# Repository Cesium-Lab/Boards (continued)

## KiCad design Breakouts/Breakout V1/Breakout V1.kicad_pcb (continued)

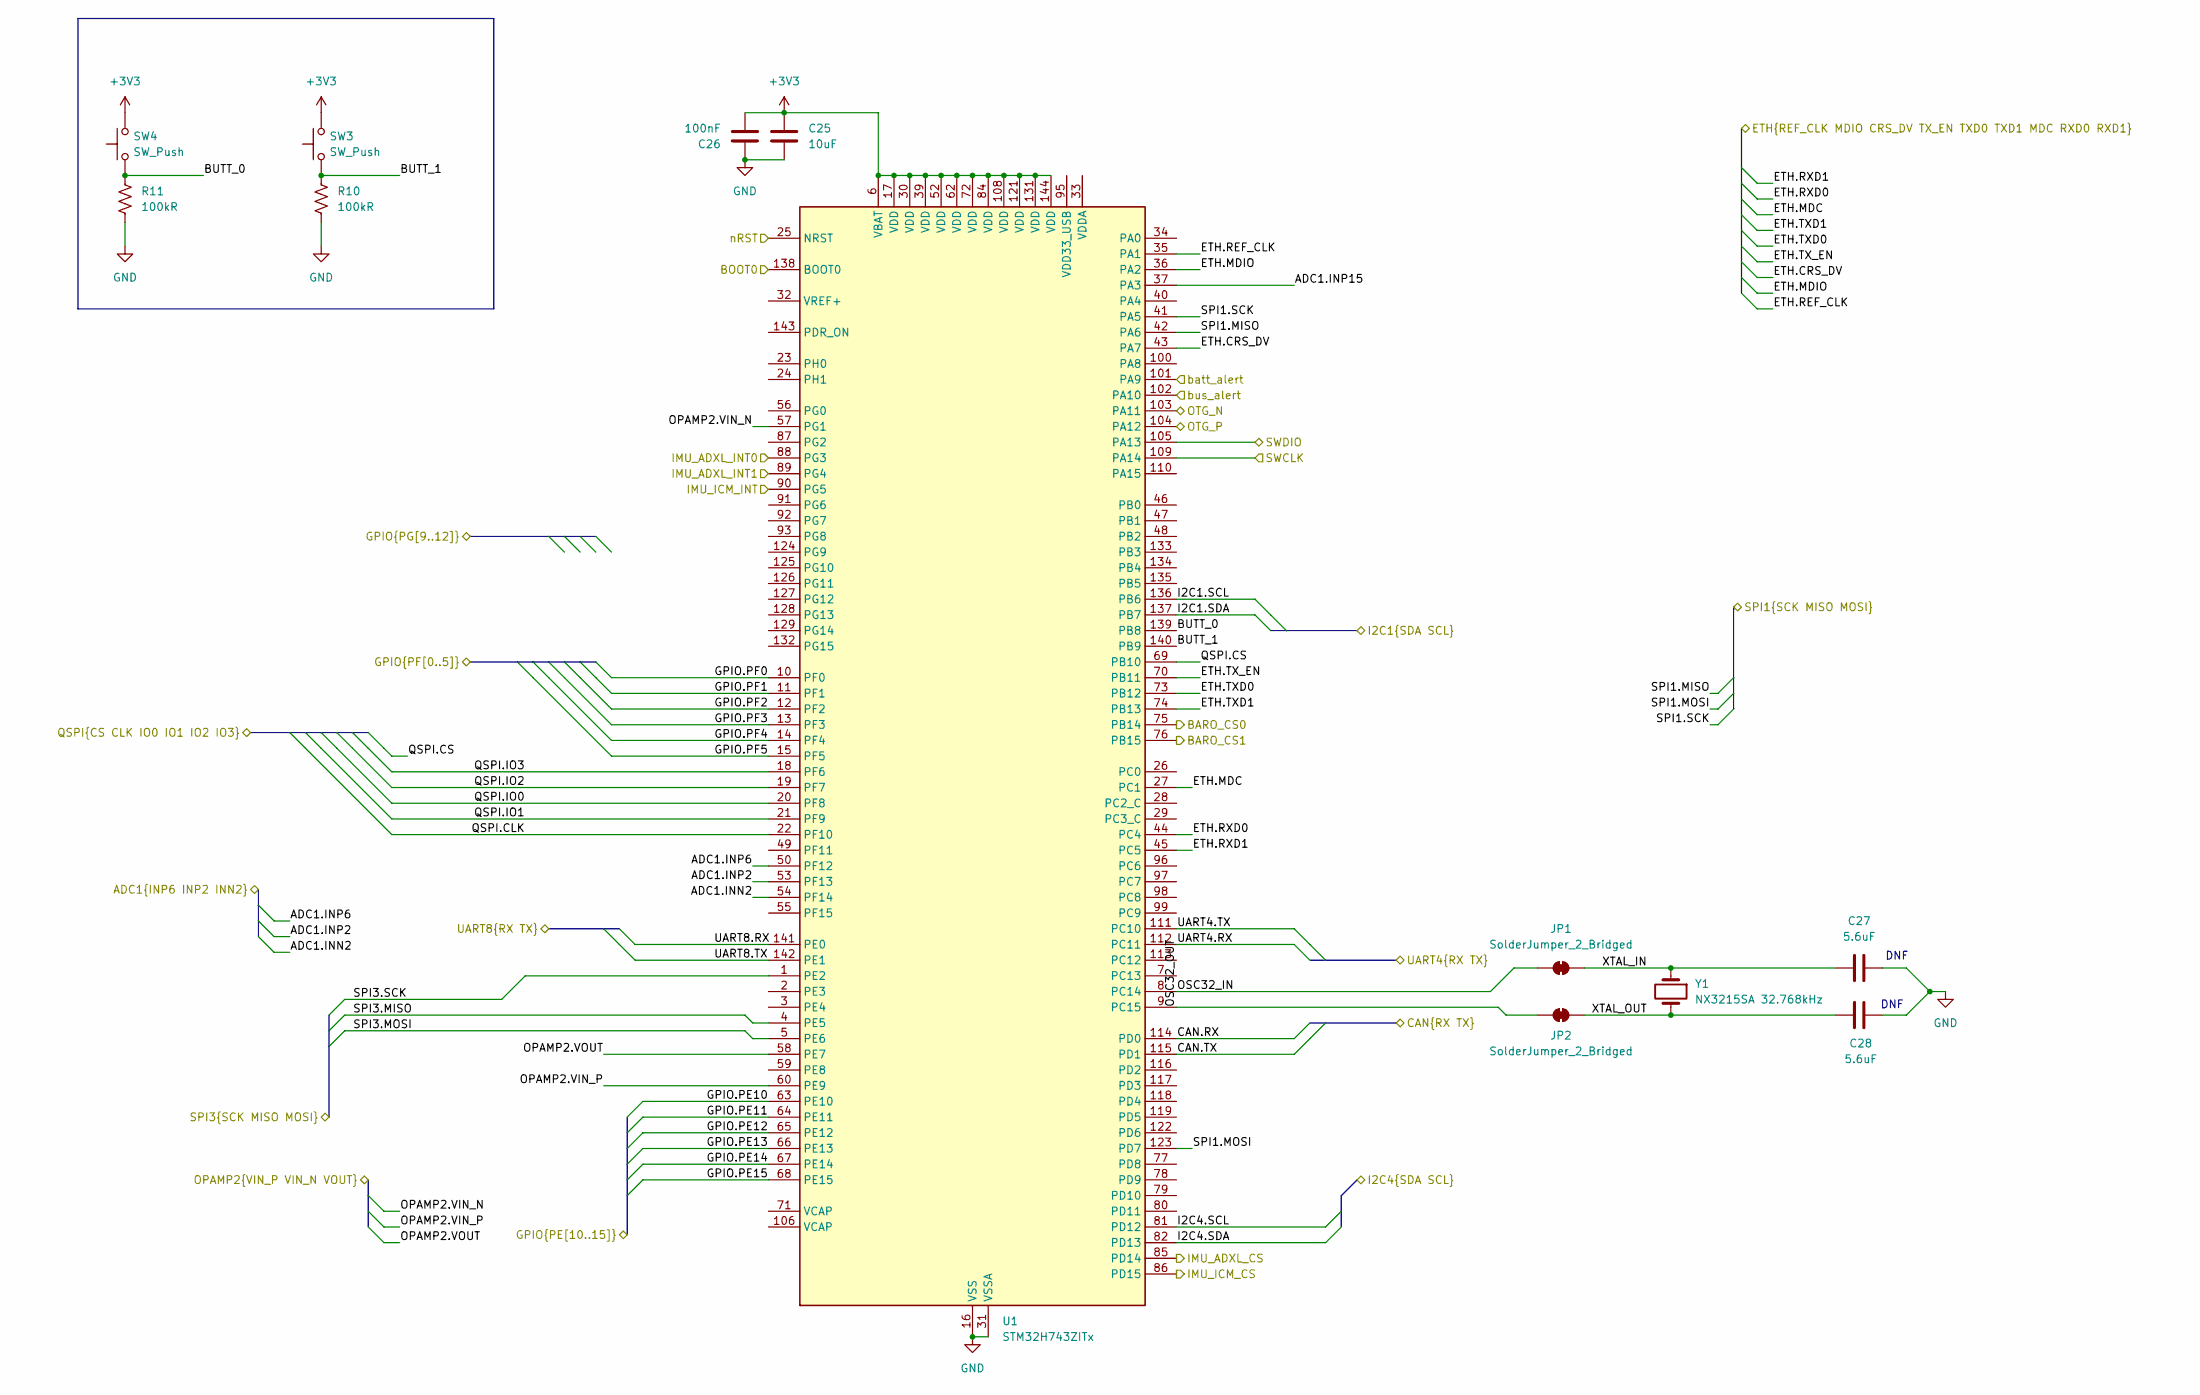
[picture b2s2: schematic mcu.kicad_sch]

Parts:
C25: 10uF; C_0603_1608Metric
C26: 100nF; C_0603_1608Metric
C27, C28: 5.6uF; C_0603_1608Metric
JP1, JP2: SolderJumper_2_Bridged; SolderJumper-2_P1.3mm_Bridged_Pad1.0x1.5mm
R10, R11: 100kR; R_0603_1608Metric
SW3, SW4: SW_Push; SW_SPST_EVPBF
U1: STM32H743ZITx; LQFP-144_20x20mm_P0.5mm
Y1: NX3215SA 32.768kHz; L_1206_3216Metric

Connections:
+3V3: C25.1, C26.2, SW3.2, SW4.2, U1.6 (VBAT), U1.17 (VDD), U1.30 (VDD), U1.39 (VDD), U1.52 (VDD), U1.62 (VDD), U1.72 (VDD), U1.84 (VDD), U1.108 (VDD), U1.121 (VDD), U1.131 (VDD), U1.144 (VDD); also elsewhere on the board
/ADXL375/CS: U1.85 (PD14); also elsewhere on the board
/ADXL375/INT1: U1.89 (PG4); also elsewhere on the board
/ADXL375/INT2: U1.88 (PG3); also elsewhere on the board
/ADXL375/SPI.MISO: U1.4 (PE5); also elsewhere on the board
/ADXL375/SPI.MOSI: U1.5 (PE6); also elsewhere on the board
/ADXL375/SPI.SCK: U1.1 (PE2); also elsewhere on the board
/Ethernet/ETH.CRS_DV: U1.43 (PA7); also elsewhere on the board
/Ethernet/ETH.MDC: U1.27 (PC1); also elsewhere on the board
/Ethernet/ETH.MDIO: U1.36 (PA2); also elsewhere on the board
/Ethernet/ETH.REF_CLK: U1.35 (PA1); also elsewhere on the board
/Ethernet/ETH.RXD0: U1.44 (PC4); also elsewhere on the board
/Ethernet/ETH.RXD1: U1.45 (PC5); also elsewhere on the board
/Ethernet/ETH.TXD0: U1.73 (PB12); also elsewhere on the board
/Ethernet/ETH.TXD1: U1.74 (PB13); also elsewhere on the board
/Ethernet/ETH.TX_EN: U1.70 (PB11); also elsewhere on the board
/Extras/ADC1.INN2: U1.54 (PF14); also elsewhere on the board
/Extras/ADC1.INP2: U1.53 (PF13); also elsewhere on the board
/Extras/ADC1.INP6: U1.50 (PF12); also elsewhere on the board
/Extras/GPIO.PE10: U1.63 (PE10); also elsewhere on the board
/Extras/GPIO.PE11: U1.64 (PE11); also elsewhere on the board
/Extras/GPIO.PE12: U1.65 (PE12); also elsewhere on the board
/Extras/GPIO.PE13: U1.66 (PE13); also elsewhere on the board
/Extras/GPIO.PE14: U1.67 (PE14); also elsewhere on the board
/Extras/GPIO.PE15: U1.68 (PE15); also elsewhere on the board
/Extras/GPIO.PF0: U1.10 (PF0); also elsewhere on the board
/Extras/GPIO.PF1: U1.11 (PF1); also elsewhere on the board
/Extras/GPIO.PF2: U1.12 (PF2); also elsewhere on the board
/Extras/GPIO.PF3: U1.13 (PF3); also elsewhere on the board
/Extras/GPIO.PF4: U1.14 (PF4); also elsewhere on the board
/Extras/GPIO.PF5: U1.15 (PF5); also elsewhere on the board
/Extras/OPAMP2.VIN_N: U1.57 (PG1); also elsewhere on the board
/Extras/OPAMP2.VIN_P: U1.60 (PE9); also elsewhere on the board
/Extras/OPAMP2.VOUT: U1.58 (PE7); also elsewhere on the board
/Extras/QSPI.CLK: U1.22 (PF10); also elsewhere on the board
/Extras/QSPI.CS: U1.69 (PB10); also elsewhere on the board
/Extras/QSPI.IO0: U1.20 (PF8); also elsewhere on the board
/Extras/QSPI.IO1: U1.21 (PF9); also elsewhere on the board
/Extras/QSPI.IO2: U1.19 (PF7); also elsewhere on the board
/Extras/QSPI.IO3: U1.18 (PF6); also elsewhere on the board
/Flashing/BOOT0: U1.138 (BOOT0); also elsewhere on the board
/Flashing/D+: U1.104 (PA12); also elsewhere on the board
/Flashing/D-: U1.103 (PA11); also elsewhere on the board
/Flashing/SWCLK: U1.109 (PA14); also elsewhere on the board
/Flashing/SWDIO: U1.105 (PA13); also elsewhere on the board
/Flashing/nRST: U1.25 (NRST); also elsewhere on the board
/IMU (2g-16g)/CS: U1.86 (PD15); also elsewhere on the board
/IMU (2g-16g)/INT: U1.90 (PG5); also elsewhere on the board
/MCU/ADC1.INP15: U1.37 (PA3)
/MCU/BARO_CS0: U1.75 (PB14); also elsewhere on the board
/MCU/BARO_CS1: U1.76 (PB15); also elsewhere on the board
/MCU/BUTT_0: R11.1, SW4.1, U1.139 (PB8)
/MCU/BUTT_1: R10.1, SW3.1, U1.140 (PB9)
/MCU/CAN.RX: U1.114 (PD0); also elsewhere on the board
/MCU/CAN.TX: U1.115 (PD1); also elsewhere on the board
/MCU/I2C1.SCL: U1.136 (PB6); also elsewhere on the board
/MCU/I2C1.SDA: U1.137 (PB7); also elsewhere on the board
/MCU/I2C4.SCL: U1.81 (PD12); also elsewhere on the board
/MCU/I2C4.SDA: U1.82 (PD13); also elsewhere on the board
/MCU/OSC32_IN: JP1.1 (A), U1.8 (PC14)
/MCU/OSC32_OUT: JP2.1 (A), U1.9 (PC15)
/MCU/SPI1.MISO: U1.42 (PA6); also elsewhere on the board
/MCU/SPI1.MOSI: U1.123 (PD7); also elsewhere on the board
/MCU/SPI1.SCK: U1.41 (PA5); also elsewhere on the board
/MCU/UART4.RX: U1.112 (PC11); also elsewhere on the board
/MCU/UART4.TX: U1.111 (PC10); also elsewhere on the board
/MCU/UART8.RX: U1.141 (PE0); also elsewhere on the board
/MCU/UART8.TX: U1.142 (PE1); also elsewhere on the board
/MCU/XTAL_IN: C27.1, JP1.2 (B), Y1.1
/MCU/XTAL_OUT: C28.1, JP2.2 (B), Y1.2
/MCU/batt_alert: U1.101 (PA9); also elsewhere on the board
/MCU/bus_alert: U1.102 (PA10); also elsewhere on the board
GND: C25.2, C26.1, C27.2, C28.2, R10.2, R11.2, U1.16 (VSS), U1.31 (VSSA), U1.38 (VSS), U1.51 (VSS), U1.61 (VSS), U1.83 (VSS), U1.94 (VSS), U1.107 (VSS), U1.120 (VSS), U1.130 (VSS); also elsewhere on the board

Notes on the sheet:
DNF

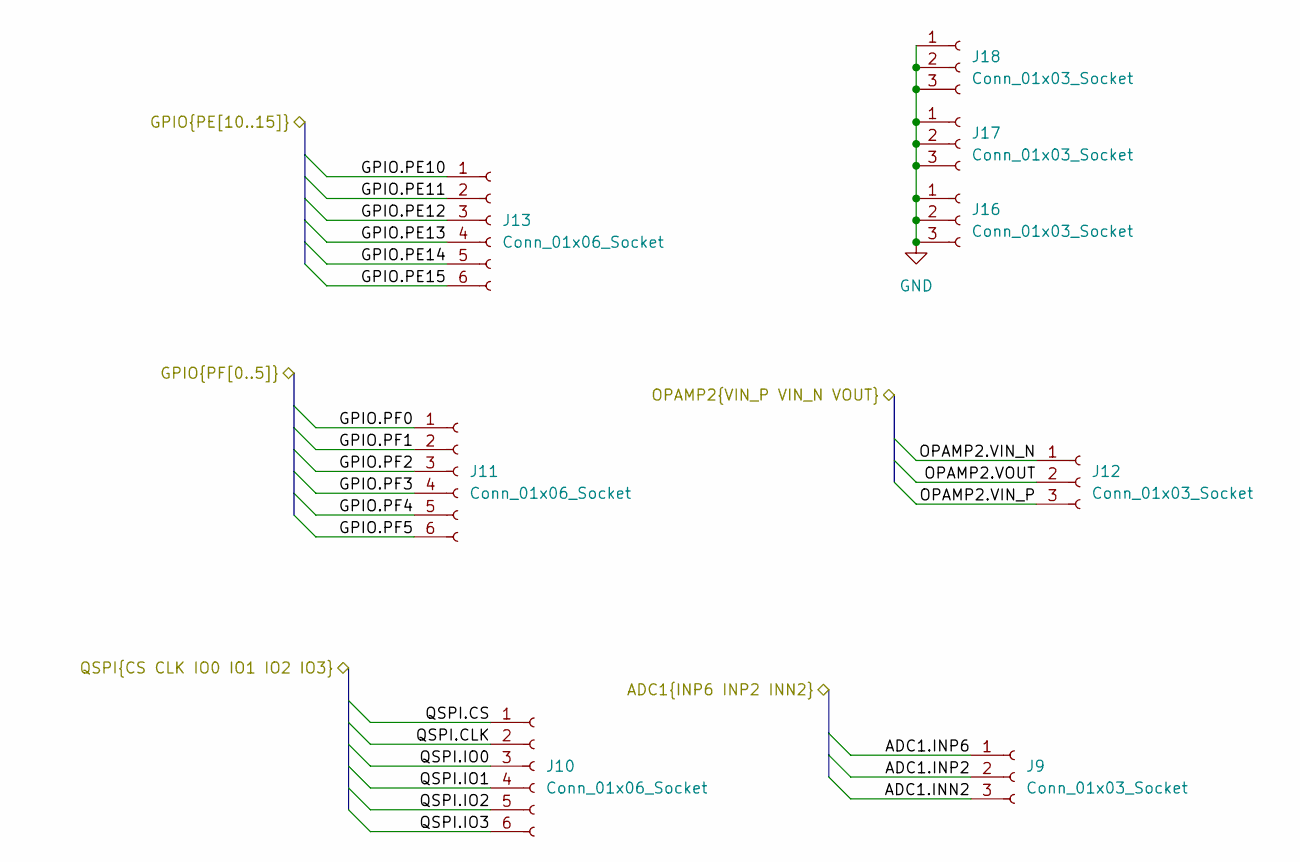
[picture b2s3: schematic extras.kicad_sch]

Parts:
J9, J12, J16, J17, J18: Conn_01x03_Socket; PinHeader_1x03_P2.54mm_Vertical
J10, J11, J13: Conn_01x06_Socket; PinHeader_1x06_P2.54mm_Vertical

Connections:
/Extras/ADC1.INN2: J9.3; also elsewhere on the board
/Extras/ADC1.INP2: J9.2; also elsewhere on the board
/Extras/ADC1.INP6: J9.1; also elsewhere on the board
/Extras/GPIO.PE10: J13.1; also elsewhere on the board
/Extras/GPIO.PE11: J13.2; also elsewhere on the board
/Extras/GPIO.PE12: J13.3; also elsewhere on the board
/Extras/GPIO.PE13: J13.4; also elsewhere on the board
/Extras/GPIO.PE14: J13.5; also elsewhere on the board
/Extras/GPIO.PE15: J13.6; also elsewhere on the board
/Extras/GPIO.PF0: J11.1; also elsewhere on the board
/Extras/GPIO.PF1: J11.2; also elsewhere on the board
/Extras/GPIO.PF2: J11.3; also elsewhere on the board
/Extras/GPIO.PF3: J11.4; also elsewhere on the board
/Extras/GPIO.PF4: J11.5; also elsewhere on the board
/Extras/GPIO.PF5: J11.6; also elsewhere on the board
/Extras/OPAMP2.VIN_N: J12.1; also elsewhere on the board
/Extras/OPAMP2.VIN_P: J12.3; also elsewhere on the board
/Extras/OPAMP2.VOUT: J12.2; also elsewhere on the board
/Extras/QSPI.CLK: J10.2; also elsewhere on the board
/Extras/QSPI.CS: J10.1; also elsewhere on the board
/Extras/QSPI.IO0: J10.3; also elsewhere on the board
/Extras/QSPI.IO1: J10.4; also elsewhere on the board
/Extras/QSPI.IO2: J10.5; also elsewhere on the board
/Extras/QSPI.IO3: J10.6; also elsewhere on the board
GND: J16.1, J16.2, J16.3, J17.1, J17.2, J17.3, J18.1, J18.2, J18.3; also elsewhere on the board

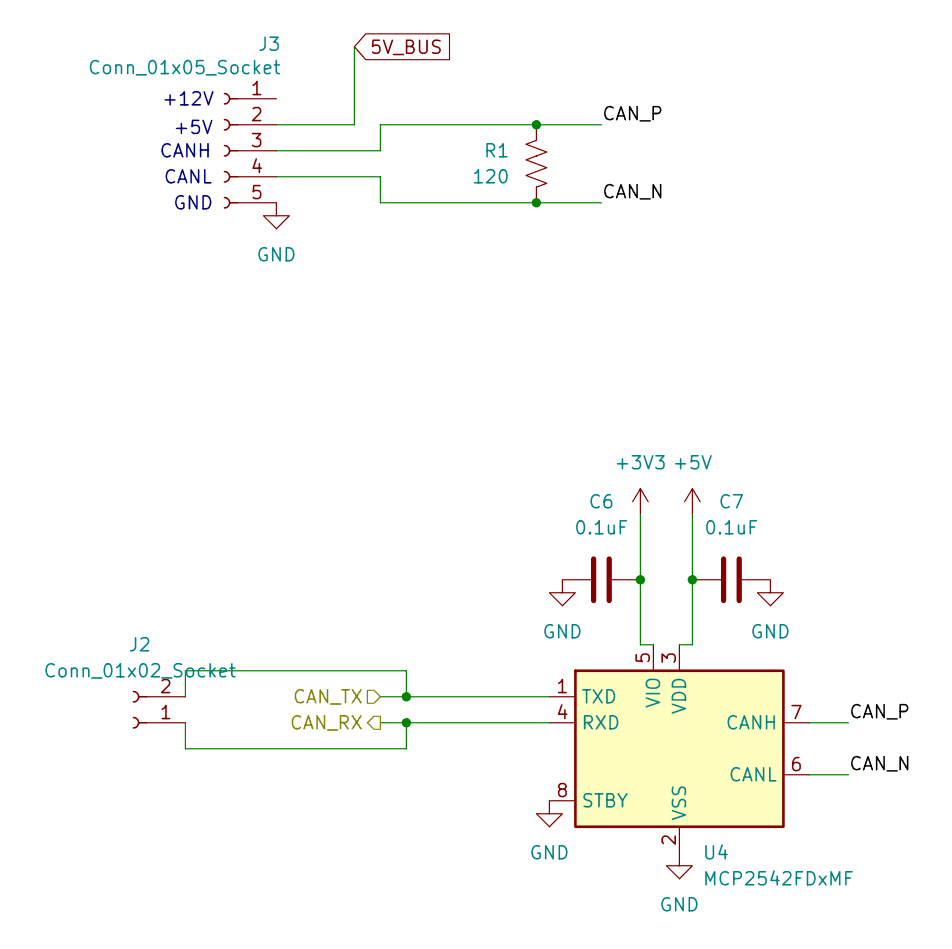
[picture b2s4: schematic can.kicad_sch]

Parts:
C6, C7: 0.1uF; C_0603_1608Metric
J2: Conn_01x02_Socket; PinHeader_1x02_P2.54mm_Vertical
J3: Conn_01x05_Socket; PinHeader_1x05_P2.54mm_Vertical
R1: 120; R_0603_1608Metric
U4: MCP2542FDxMF; DFN-8-1EP_3x3mm_P0.65mm_EP1.55x2.4mm

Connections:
5V_BUS: J3.2; also elsewhere on the board
+3V3: C6.2, U4.5 (VIO); also elsewhere on the board
+5V: C7.1, U4.3 (VDD); also elsewhere on the board
/CAN/CAN_N: J3.4, R1.2, U4.6 (CANL)
/CAN/CAN_P: J3.3, R1.1, U4.7 (CANH)
/MCU/CAN.RX: J2.1, U4.4 (RXD); also elsewhere on the board
/MCU/CAN.TX: J2.2, U4.1 (TXD); also elsewhere on the board
GND: C6.1, C7.2, J3.5, U4.2 (VSS), U4.8 (STBY), U4.9 (VSS); also elsewhere on the board

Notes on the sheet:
CANH
+5V
+12V
GND
CANL

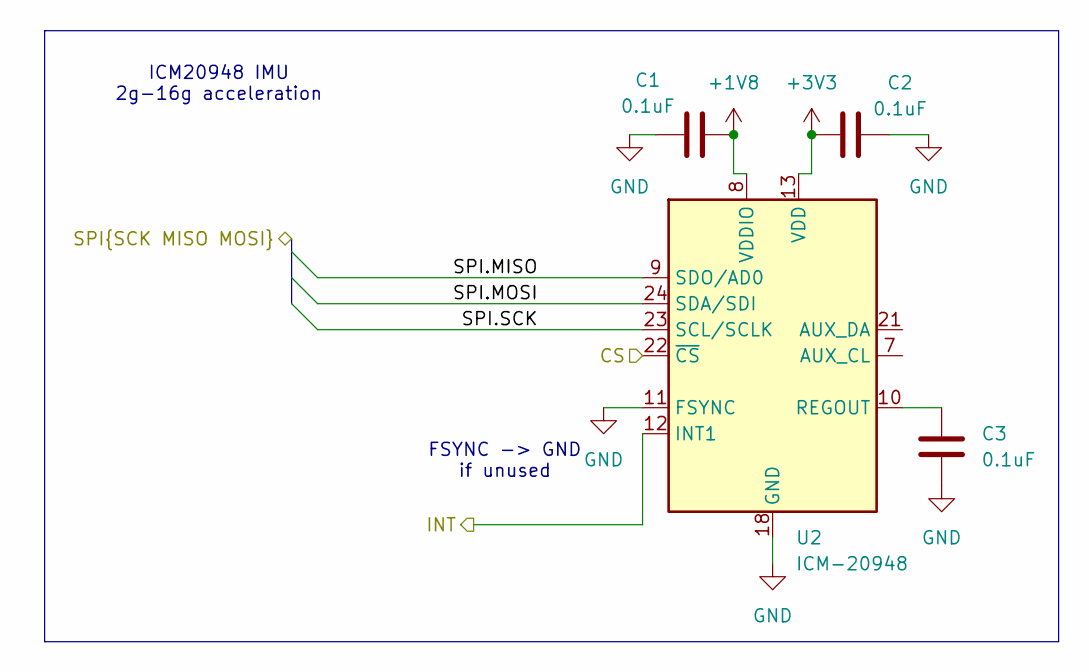
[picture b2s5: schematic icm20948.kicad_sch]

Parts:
C1, C2, C3: 0.1uF; C_0603_1608Metric
U2: ICM-20948; InvenSense_QFN-24_3x3mm_P0.4mm

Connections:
+1V8: C1.2, U2.8 (VDDIO); also elsewhere on the board
+3V3: C2.1, U2.13 (VDD); also elsewhere on the board
/ADXL375/SPI.MISO: U2.9 (SDO/AD0); also elsewhere on the board
/ADXL375/SPI.MOSI: U2.24 (SDA/SDI); also elsewhere on the board
/ADXL375/SPI.SCK: U2.23 (SCL/SCLK); also elsewhere on the board
/IMU (2g-16g)/CS: U2.22 (~CS); also elsewhere on the board
/IMU (2g-16g)/INT: U2.12 (INT1); also elsewhere on the board
GND: C1.1, C2.2, C3.2, U2.11 (FSYNC), U2.18 (GND), U2.20 (GND); also elsewhere on the board
unnamed: C3.1, U2.10 (REGOUT)

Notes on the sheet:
ICM20948 IMU 2g-16g acceleration
FSYNC -> GND if unused

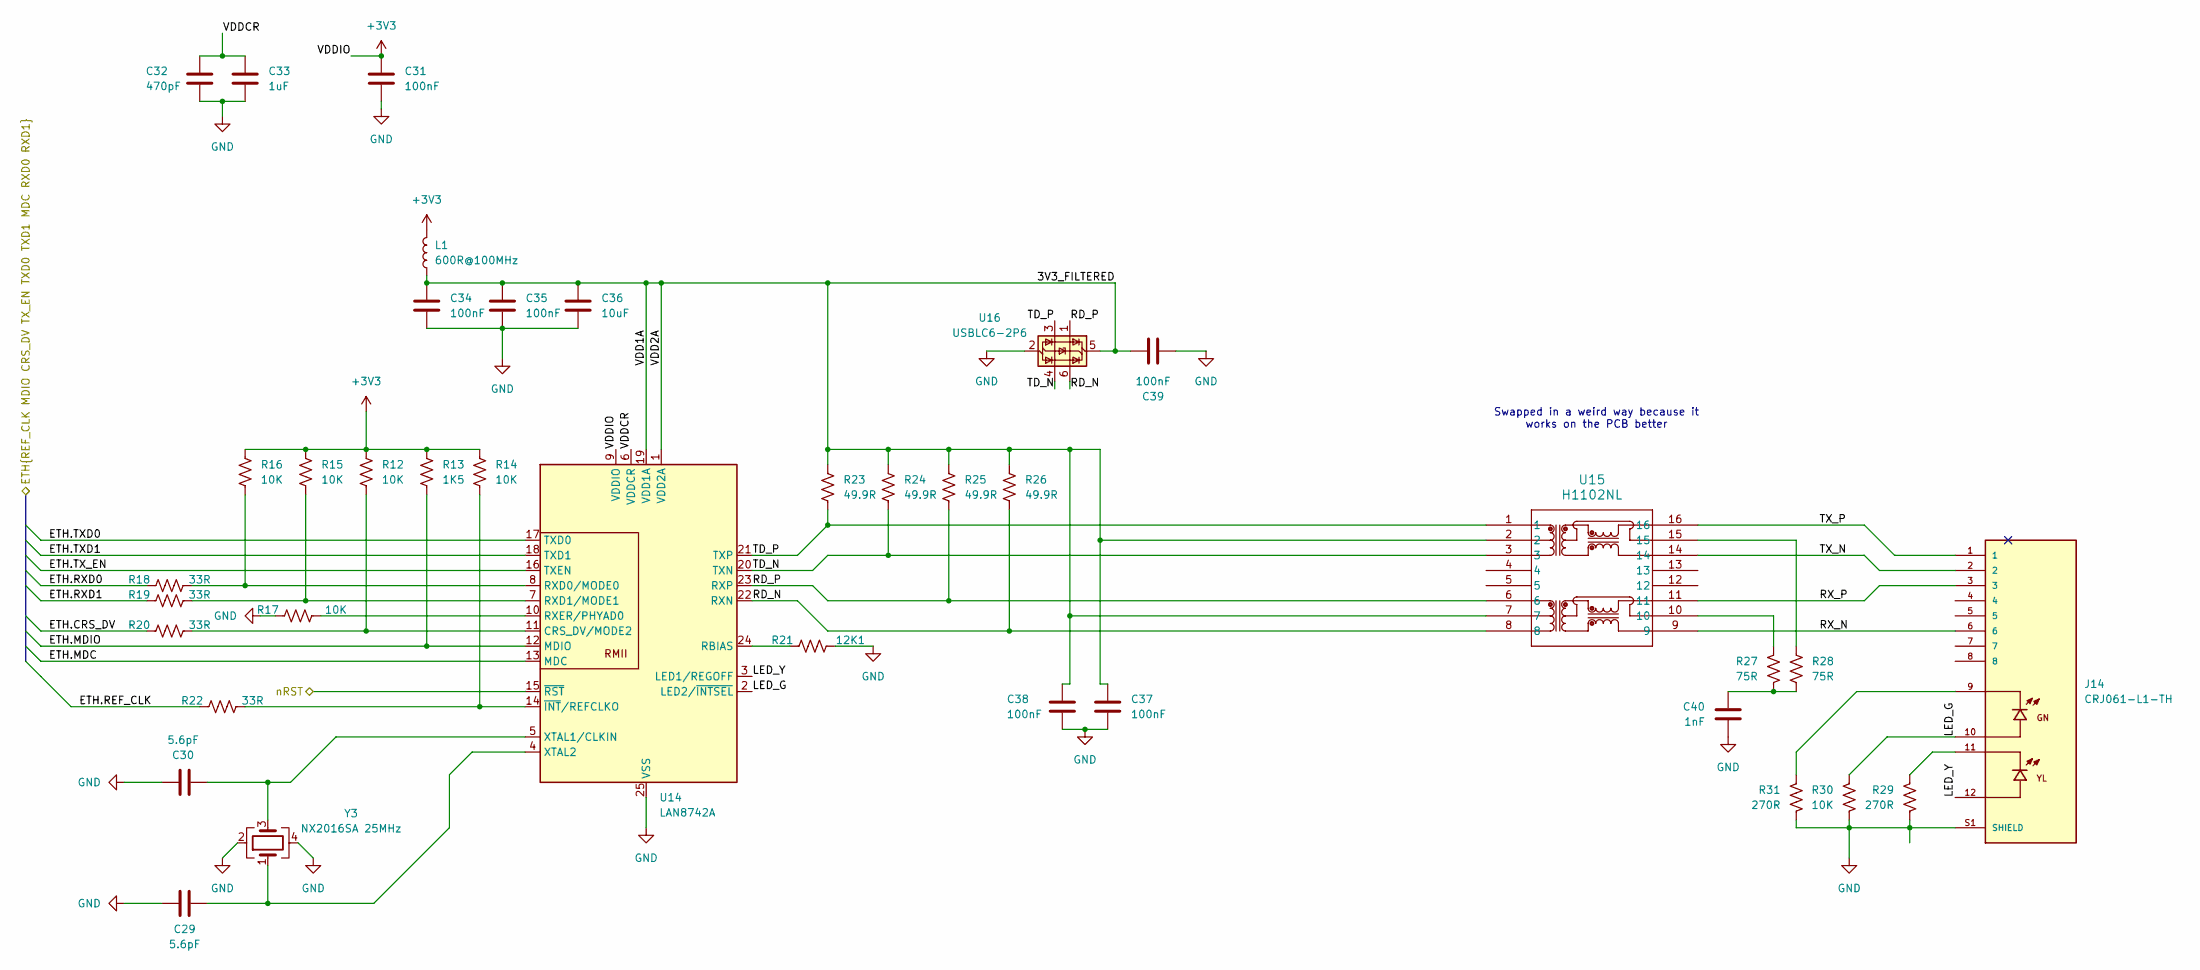
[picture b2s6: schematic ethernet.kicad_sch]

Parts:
C29, C30: 5.6pF; C_0603_1608Metric
C31, C34, C35, C37, C38, C39: 100nF; C_0603_1608Metric
C32: 470pF; C_0603_1608Metric
C33: 1uF; C_0603_1608Metric
C36: 10uF; C_0603_1608Metric
C40: 1nF; C_0603_1608Metric
J14: CRJ061-L1-TH; CUI_CRJ061-L1-TH; PARTREV 1.0; DigiKey_Part_Number 2223-CRJ061-L1-TH-ND
L1: 600R@100MHz; C_0603_1608Metric
R12, R14, R15, R16, R17, R30: 10K; R_0603_1608Metric
R13: 1K5; R_0603_1608Metric
R18, R19, R20, R22: 33R; R_0603_1608Metric
R21: 12K1; R_0603_1608Metric
R23, R24, R25, R26: 49.9R; R_0603_1608Metric
R27, R28: 75R; R_0603_1608Metric
R29, R31: 270R; R_0603_1608Metric
U14: LAN8742A; VQFN-24-1EP_4x4mm_P0.5mm_EP2.5x2.5mm_ThermalVias
U15: H1102NL; Transformer_Pulse_H1100NL
U16: USBLC6-2P6; SOT-666
Y3: NX2016SA 25MHz; Crystal_SMD_1210-4Pin_1.2x1.0mm

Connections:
+3V3: C31.1, L1.2, R12.1, R13.1, R14.1, R15.1, R16.1, U14.9 (VDDIO); also elsewhere on the board
/Ethernet/3V3_FILTERED: C34.1, C35.1, C36.1, C37.1, C38.2, C39.2, L1.1, R23.1, R24.1, R25.1, R26.1, U14.1 (VDD2A), U14.19 (VDD1A), U15.2, U15.7, U16.5 (VBUS)
/Ethernet/ETH.CRS_DV: R20.1; also elsewhere on the board
/Ethernet/ETH.MDC: U14.13 (MDC); also elsewhere on the board
/Ethernet/ETH.MDIO: R13.2, U14.12 (MDIO); also elsewhere on the board
/Ethernet/ETH.REF_CLK: R22.1; also elsewhere on the board
/Ethernet/ETH.RXD0: R18.1; also elsewhere on the board
/Ethernet/ETH.RXD1: R19.1; also elsewhere on the board
/Ethernet/ETH.TXD0: U14.17 (TXD0); also elsewhere on the board
/Ethernet/ETH.TXD1: U14.18 (TXD1); also elsewhere on the board
/Ethernet/ETH.TX_EN: U14.16 (TXEN); also elsewhere on the board
/Ethernet/LED_G: J14.10, R30.1, U14.2 (LED2/~INTSEL)
/Ethernet/LED_Y: J14.12, U14.3 (LED1/REGOFF)
/Ethernet/RD_N: R26.2, U14.22 (RXN), U15.8, U16.6 (I/O1)
/Ethernet/RD_P: R25.2, U14.23 (RXP), U15.6, U16.1 (I/O1)
/Ethernet/RX_N: J14.6, U15.9
/Ethernet/RX_P: J14.3, U15.11
/Ethernet/TD_N: R24.2, U14.20 (TXN), U15.3, U16.4 (I/O2)
/Ethernet/TD_P: R23.2, U14.21 (TXP), U15.1, U16.3 (I/O2)
/Ethernet/TX_N: J14.2, U15.14
/Ethernet/TX_P: J14.1, U15.16
/Ethernet/VDDCR: C32.1, C33.1, U14.6 (VDDCR)
/Flashing/nRST: U14.15 (~RST); also elsewhere on the board
GND: C29.1, C30.2, C31.2, C32.2, C33.2, C34.2, C35.2, C36.2, C37.2, C38.1, C39.1, C40.2, J14.S1 (SHIELD), J14.S2 (SHIELD), R17.1, R21.2, R29.2, R30.2, R31.2, U14.25 (VSS), U16.2 (GND), Y3.2, Y3.4; also elsewhere on the board
unnamed: C40.1, R27.2, R28.2
unnamed: J14.9, R31.1
unnamed: J14.11, R29.1
unnamed: R27.1, U15.10
unnamed: R28.1, U15.15
unnamed: R12.2, R20.2, U14.11 (CRS_DV/MODE2)
unnamed: R21.1, U14.24 (RBIAS)
unnamed: R16.2, R18.2, U14.8 (RXD0/MODE0)
unnamed: R15.2, R19.2, U14.7 (RXD1/MODE1)
unnamed: R17.2, U14.10 (RXER/PHYAD0)
unnamed: C30.1, U14.5 (XTAL1/CLKIN), Y3.3
unnamed: C29.2, U14.4 (XTAL2), Y3.1
unnamed: R14.2, R22.2, U14.14 (~INT/REFCLKO)

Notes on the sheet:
Swapped in a weird way because it works on the PCB better

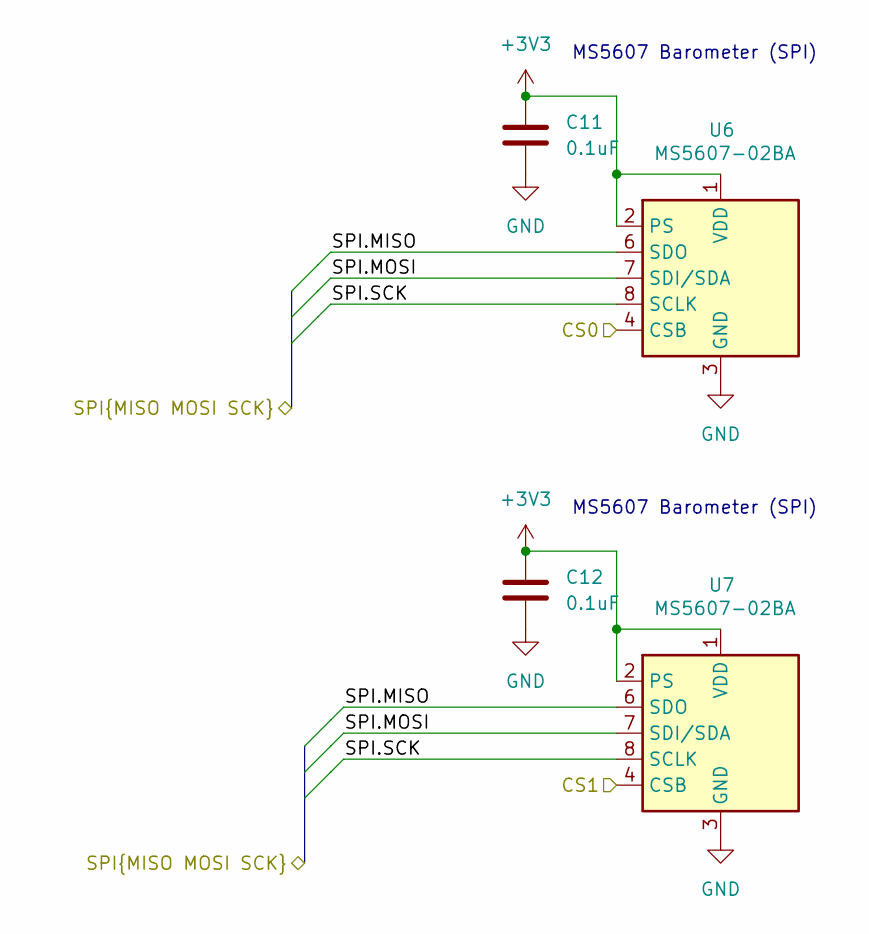
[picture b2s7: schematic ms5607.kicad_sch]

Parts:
C11, C12: 0.1uF; C_0603_1608Metric
U6, U7: MS5607-02BA; LGA-8_3x5mm_P1.25mm

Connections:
+3V3: C11.1, C12.1, U6.1 (VDD), U6.2 (PS), U7.1 (VDD), U7.2 (PS); also elsewhere on the board
/MCU/BARO_CS0: U6.4 (CSB), U6.5 (CSB); also elsewhere on the board
/MCU/BARO_CS1: U7.4 (CSB), U7.5 (CSB); also elsewhere on the board
/MCU/SPI1.MISO: U6.6 (SDO), U7.6 (SDO); also elsewhere on the board
/MCU/SPI1.MOSI: U6.7 (SDI/SDA), U7.7 (SDI/SDA); also elsewhere on the board
/MCU/SPI1.SCK: U6.8 (SCLK), U7.8 (SCLK); also elsewhere on the board
GND: C11.2, C12.2, U6.3 (GND), U7.3 (GND); also elsewhere on the board

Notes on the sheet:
MS5607 Barometer (SPI)

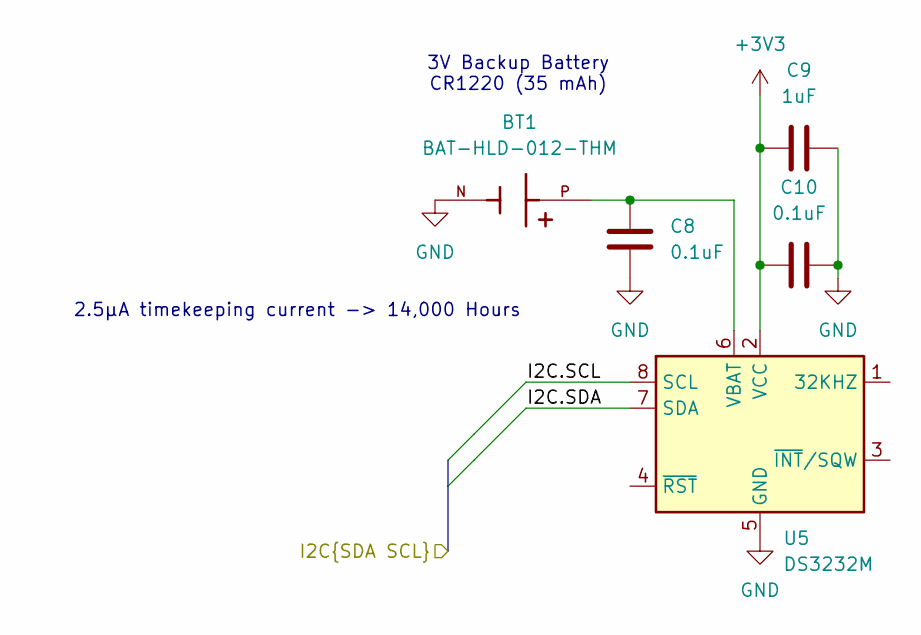
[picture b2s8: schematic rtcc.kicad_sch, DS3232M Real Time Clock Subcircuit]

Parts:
BT1: BAT-HLD-012-THM; BatteryHolder_LINX_BAT-HLD-012-SMT
C8, C10: 0.1uF; C_0603_1608Metric
C9: 1uF; C_0603_1608Metric
U5: DS3232M; SOIC-8_3.9x4.9mm_P1.27mm

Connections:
+3V3: C9.1, C10.1, U5.2 (VCC); also elsewhere on the board
/MCU/I2C1.SCL: U5.8 (SCL); also elsewhere on the board
/MCU/I2C1.SDA: U5.7 (SDA); also elsewhere on the board
GND: BT1.N, C8.1, C9.2, C10.2, U5.5 (GND); also elsewhere on the board
unnamed: BT1.P, C8.2, U5.6 (VBAT)

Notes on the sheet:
2.5µA timekeeping current -> 14,000 Hours
3V Backup Battery CR1220 (35 mAh)

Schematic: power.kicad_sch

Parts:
5V1: 5V; PinHeader_1x01_P2.54mm_Vertical
C15, C23, C24: 0.1uF; C_0603_1608Metric
C16, C17, C18, C19, C20: 10uF; C_0603_1608Metric
C21: 22uF; C_0603_1608Metric
C22: 47uF; C_0603_1608Metric
D2, D3, D4: GREEN; LED_0603_1608Metric_Pad1.05x0.95mm_HandSolder
D5, D6, D7, D8: D; D_0603_1608Metric
F2: Polyfuse; Fuse_1206_3216Metric
J6: Conn_01x02; AMASS_XT60-M_1x02_P7.20mm_Vertical
R4: 220; R_0603_1608Metric
R5, R6, R9, R32: 1k; R_0603_1608Metric
R7, R8: 200m; R_0603_1608Metric
TP1: V_BUS; PinHeader_1x01_P2.54mm_Vertical
TP2: 3V3; PinHeader_1x01_P2.54mm_Vertical
TP3: V_BATT; PinHeader_1x01_P2.54mm_Vertical
TP4: 1V8; PinHeader_1x01_P2.54mm_Vertical
TP5: V_USB; PinHeader_1x01_P2.54mm_Vertical
U9, U13: INA233; VSSOP-10_3x3mm_P0.5mm
U10: LM1085-3.3; TO-263-3_TabPin2
U11: LM1085-5.0; TO-263-3_TabPin2
U12: AMS1117-1.8; SOT-223-3_TabPin2

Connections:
5V_BUS: D8.2 (A), TP1.1; also elsewhere on the board
+1V8: C21.1, R4.2, TP4.1, U12.2 (VO); also elsewhere on the board
+3V3: C15.1, C18.1, C19.2, C24.1, R5.2, R9.2, R32.2, TP2.1, U9.6 (VS), U10.2 (VO), U12.3 (VI), U13.6 (VS); also elsewhere on the board
+5V: 5V1.1, C16.2, D5.1 (K), D6.1 (K), D7.1 (K), R6.2, U10.3 (VI); also elsewhere on the board
/Flashing/V_USB: D7.2 (A), TP5.1; also elsewhere on the board
/MCU/I2C4.SCL: U9.5 (SCL), U13.5 (SCL); also elsewhere on the board
/MCU/I2C4.SDA: U9.2 (A0), U9.4 (SDA), U13.4 (SDA); also elsewhere on the board
/MCU/batt_alert: R32.1, U9.3 (~Alert); also elsewhere on the board
/MCU/bus_alert: R9.1, U13.3 (~Alert); also elsewhere on the board
/power/5V_LDO: C20.2, D5.2 (A), U11.2 (VO)
/power/BATT_INPUT: J6.2, R7.1, TP3.1, U9.8 (Vbus), U9.10 (Vin+)
/power/V_BATT: C17.2, R7.2, U9.9 (Vin-), U11.3 (VI)
/power/V_BUS_Out: C22.1, C23.1, D6.2 (A), R8.2, U13.9 (Vin-)
GND: C15.2, C16.1, C17.1, C18.2, C19.1, C20.1, C21.2, C22.2, C23.2, C24.2, D2.1 (K), D3.1 (K), D4.1 (K), J6.1, U9.1 (A1), U9.7 (GND), U10.1 (GND), U11.1 (GND), U12.1 (GND), U13.1 (A1), U13.2 (A0), U13.7 (GND); also elsewhere on the board
unnamed: D2.2 (A), R4.1
unnamed: D3.2 (A), R5.1
unnamed: D4.2 (A), R6.1
unnamed: D8.1 (K), F2.1
unnamed: F2.2, R8.1, U13.8 (Vbus), U13.10 (Vin+)

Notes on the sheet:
Battery Input and Current Sense
Testpoints
PTS12066V200
5V LDO
Max Current: 3A
LEDs
3V3 LDO
+3V3
Max Current: 1A (only used for ICM20948)
5V_LDO
1V8 LDO
Bus Power Current Sense
A0 -> SDA A1 -> Gnd Addr: 0x42
+1V8
+5V
5V_BUS
V_USB
Optional 7.4V 2S Battery if not powered via Bus
V_BATT
5V Diodes
A0,A1 -> Gnd Addr: 0x40

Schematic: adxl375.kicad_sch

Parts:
C4: 1uF; C_0603_1608Metric
C5: 0.1uF; C_0603_1608Metric
U3: ADXL375BCCZ-RL7; LGA-14_3x5mm_P0.8mm_LayoutBorder1x6y

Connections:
+3V3: C4.1, C5.1, U3.1 (VDDI/O), U3.6 (VS); also elsewhere on the board
/ADXL375/CS: U3.7 (*CS); also elsewhere on the board
/ADXL375/INT1: U3.8 (INT1); also elsewhere on the board
/ADXL375/INT2: U3.9 (INT2); also elsewhere on the board
/ADXL375/SPI.MISO: U3.12 (SDO/ALTADDRESS); also elsewhere on the board
/ADXL375/SPI.MOSI: U3.13 (SDA/SDI/SDIO); also elsewhere on the board
/ADXL375/SPI.SCK: U3.14 (SCL/SCLK); also elsewhere on the board
GND: C4.2, C5.2, U3.2 (GND), U3.4 (GND), U3.5 (GND); also elsewhere on the board

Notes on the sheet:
ADXL375 Accelerometer 200g acceleration

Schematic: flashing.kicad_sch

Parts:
C13, C14: 0.1uF; C_0603_1608Metric
D1: D; D_0603_1608Metric
F1: 5V/3A; Fuse_0603_1608Metric
FB1: BLM21PG221; L_0603_1608Metric_Pad1.05x0.95mm_HandSolder
J4: USB_C_Receptacle_USB2.0_16P; USB_C_Receptacle_HRO_TYPE-C-31-M-12
J5: Conn_01x06_Pin; PinHeader_1x06_P2.54mm_Vertical
JP3, JP4: SolderJumper_2_Bridged; SolderJumper-2_P1.3mm_Bridged_Pad1.0x1.5mm
R2, R3: 5.1k; R_0603_1608Metric
SW1, SW2: SW_Push; SW_SPST_EVPBF
U8: USBLC6-2P6; SOT-666
U23: ESDALC6V1-1U2; D_SOD-523

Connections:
+3V3: J5.1; also elsewhere on the board
/Flashing/BOOT0: JP4.2 (B); also elsewhere on the board
/Flashing/CC1: J4.A5 (CC1), R2.1
/Flashing/CC2: J4.B5 (CC2), R3.1
/Flashing/D+: U8.4 (I/O2); also elsewhere on the board
/Flashing/D-: U8.6 (I/O1); also elsewhere on the board
/Flashing/SWCLK: J5.2; also elsewhere on the board
/Flashing/SWDIO: J5.4; also elsewhere on the board
/Flashing/USB+: J4.A6 (D+), J4.B6 (D+), U8.3 (I/O2)
/Flashing/USB-: J4.A7 (D-), J4.B7 (D-), U8.1 (I/O1)
/Flashing/VBUS: D1.2 (A), J4.A4 (VBUS), J4.A9 (VBUS), J4.B4 (VBUS), J4.B9 (VBUS)
/Flashing/V_USB: F1.1, U8.5 (VBUS); also elsewhere on the board
/Flashing/nRST: J5.5, JP3.2 (B); also elsewhere on the board
GND: C13.1, C14.1, J4.A1 (GND), J4.A12 (GND), J4.B1 (GND), J4.B12 (GND), J4.S1 (SHIELD), J5.3, R2.2, R3.2, SW1.1, SW2.1, U8.2 (GND), U23.2 (A); also elsewhere on the board
unnamed: D1.1 (K), FB1.1
unnamed: F1.2, FB1.2
unnamed: C13.2, JP3.1 (A), SW1.2, U23.1 (K)
unnamed: C14.2, JP4.1 (A), SW2.2

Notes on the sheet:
ST-LINK Connection

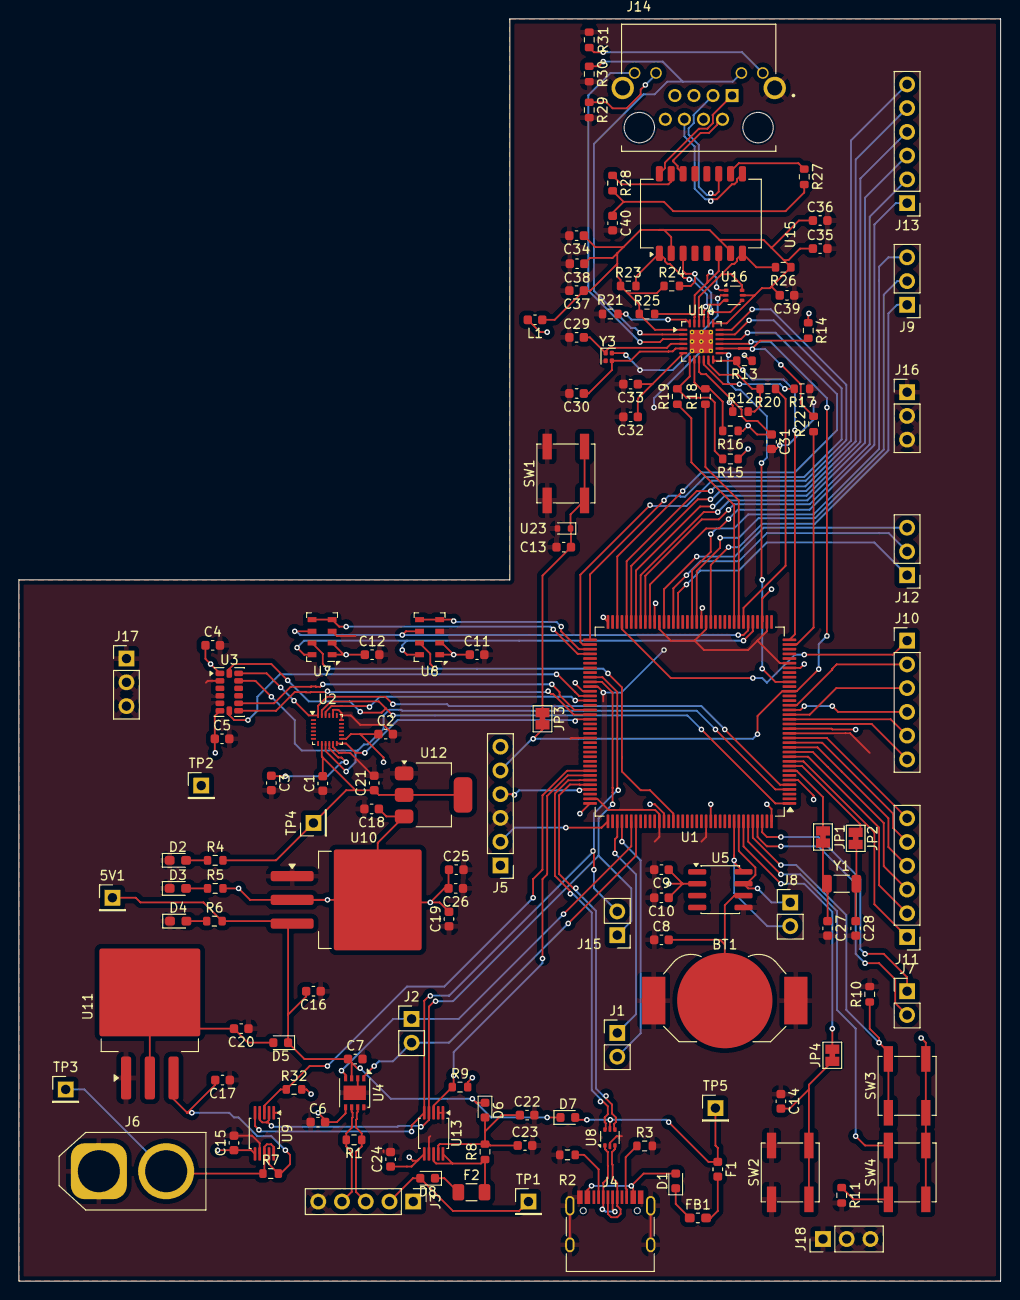
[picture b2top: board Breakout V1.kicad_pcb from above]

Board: 2 copper layers, 105.0 x 135.0 mm, 136 parts (0 on the bottom side), 123 nets.

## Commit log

2025-12-25 Breakout V1 Draft 1
2025-12-28 revA: Test Rocket
